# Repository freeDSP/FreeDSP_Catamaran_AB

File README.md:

# FreeDSP_Catamaran_AB
A dual mono construction Concept Differential ADC 1 in 4 out ADAU1701 board. Extreme High performance (ADC to DAC Overall Distortion 0.00087%) differential A/D Conversion, differential RCA-pin Outputs, fs=96kHz, 8 slots TDM-Interlink across the boards.

Features:

- 1in 4 out RCA jacks on each PCB (2 boards requires for stereo use)
- High-performance differential monaural ADAU1701 ADC circuit
- GND lift-able Differntial RCA-pin Input curcuit
- GND lift-able Differential RCA-pin Output circuit
- Mains Power Switch
- Power-ON/OFF/Reboot Anti-Pop Audio Mute
- LED Power Indicator
- MP1/MP7 controlled LED Indicators
- A/B Program Select switch with Auto-Reboot feature
- Selectable DSP reboot Dual-EEPROMs
- Rotary Pots for AUXADC 0-3
- interlink header for AUXADC control voltage 0-3 and Reset
- Common-mode Choke filtered Power Supply Input
- 0805(2.0mm x 1.25mm) SMD Resistors & Capacitors
- Prepare for the through-hole Ele-Caps on the Audio Path
- Unity Gain Analog Audio Input and Output (2V RMS)
- Absolute Phase transparent. (No need to invert Output Phase)
- Buffered TDM Interlink I/O Header (with Enable control)
- JST-EH Connectors for Optional XLR output driver board.

PCBA file package included in JLPCB_OrderFiles. You can order SMT and Boards. (https://jlcpcb.com/) 

A Wiki Page(https://github.com/freeDSP/FreeDSP_Catamaran_AB/wiki) of this project

Discussion forum thread (https://www.diyaudio.com/community/threads/freedsp-catamaran-a-b.381417/)

Project web page: (Direct Link) https://cyberpithilo.web.fc2.com/audio/freedsp/index.html

Project web page: (Yandex Machine Translation) https://translate.yandex.com/translate?url=https%3A%2F%2Fcyberpithilo.web.fc2.com%2Faudio%2Ffreedsp%2Fcatamaran_main.html&lang=ja-en

Project web page: (Google Machine Translation) https://cyberpithilo-web-fc2-com.translate.goog/audio/freedsp/catamaran_main.html?_x_tr_sl=ja&_x_tr_tl=en&_x_tr_hl=ja

# License
This work and all other materials under https://github.com/freeDSP are licensed under a Creative Commons Attribution Share-Alike 4.0 license. This allows for both personal and commercial derivative works, as long as they credit freeDSP and release their designs under the same license.

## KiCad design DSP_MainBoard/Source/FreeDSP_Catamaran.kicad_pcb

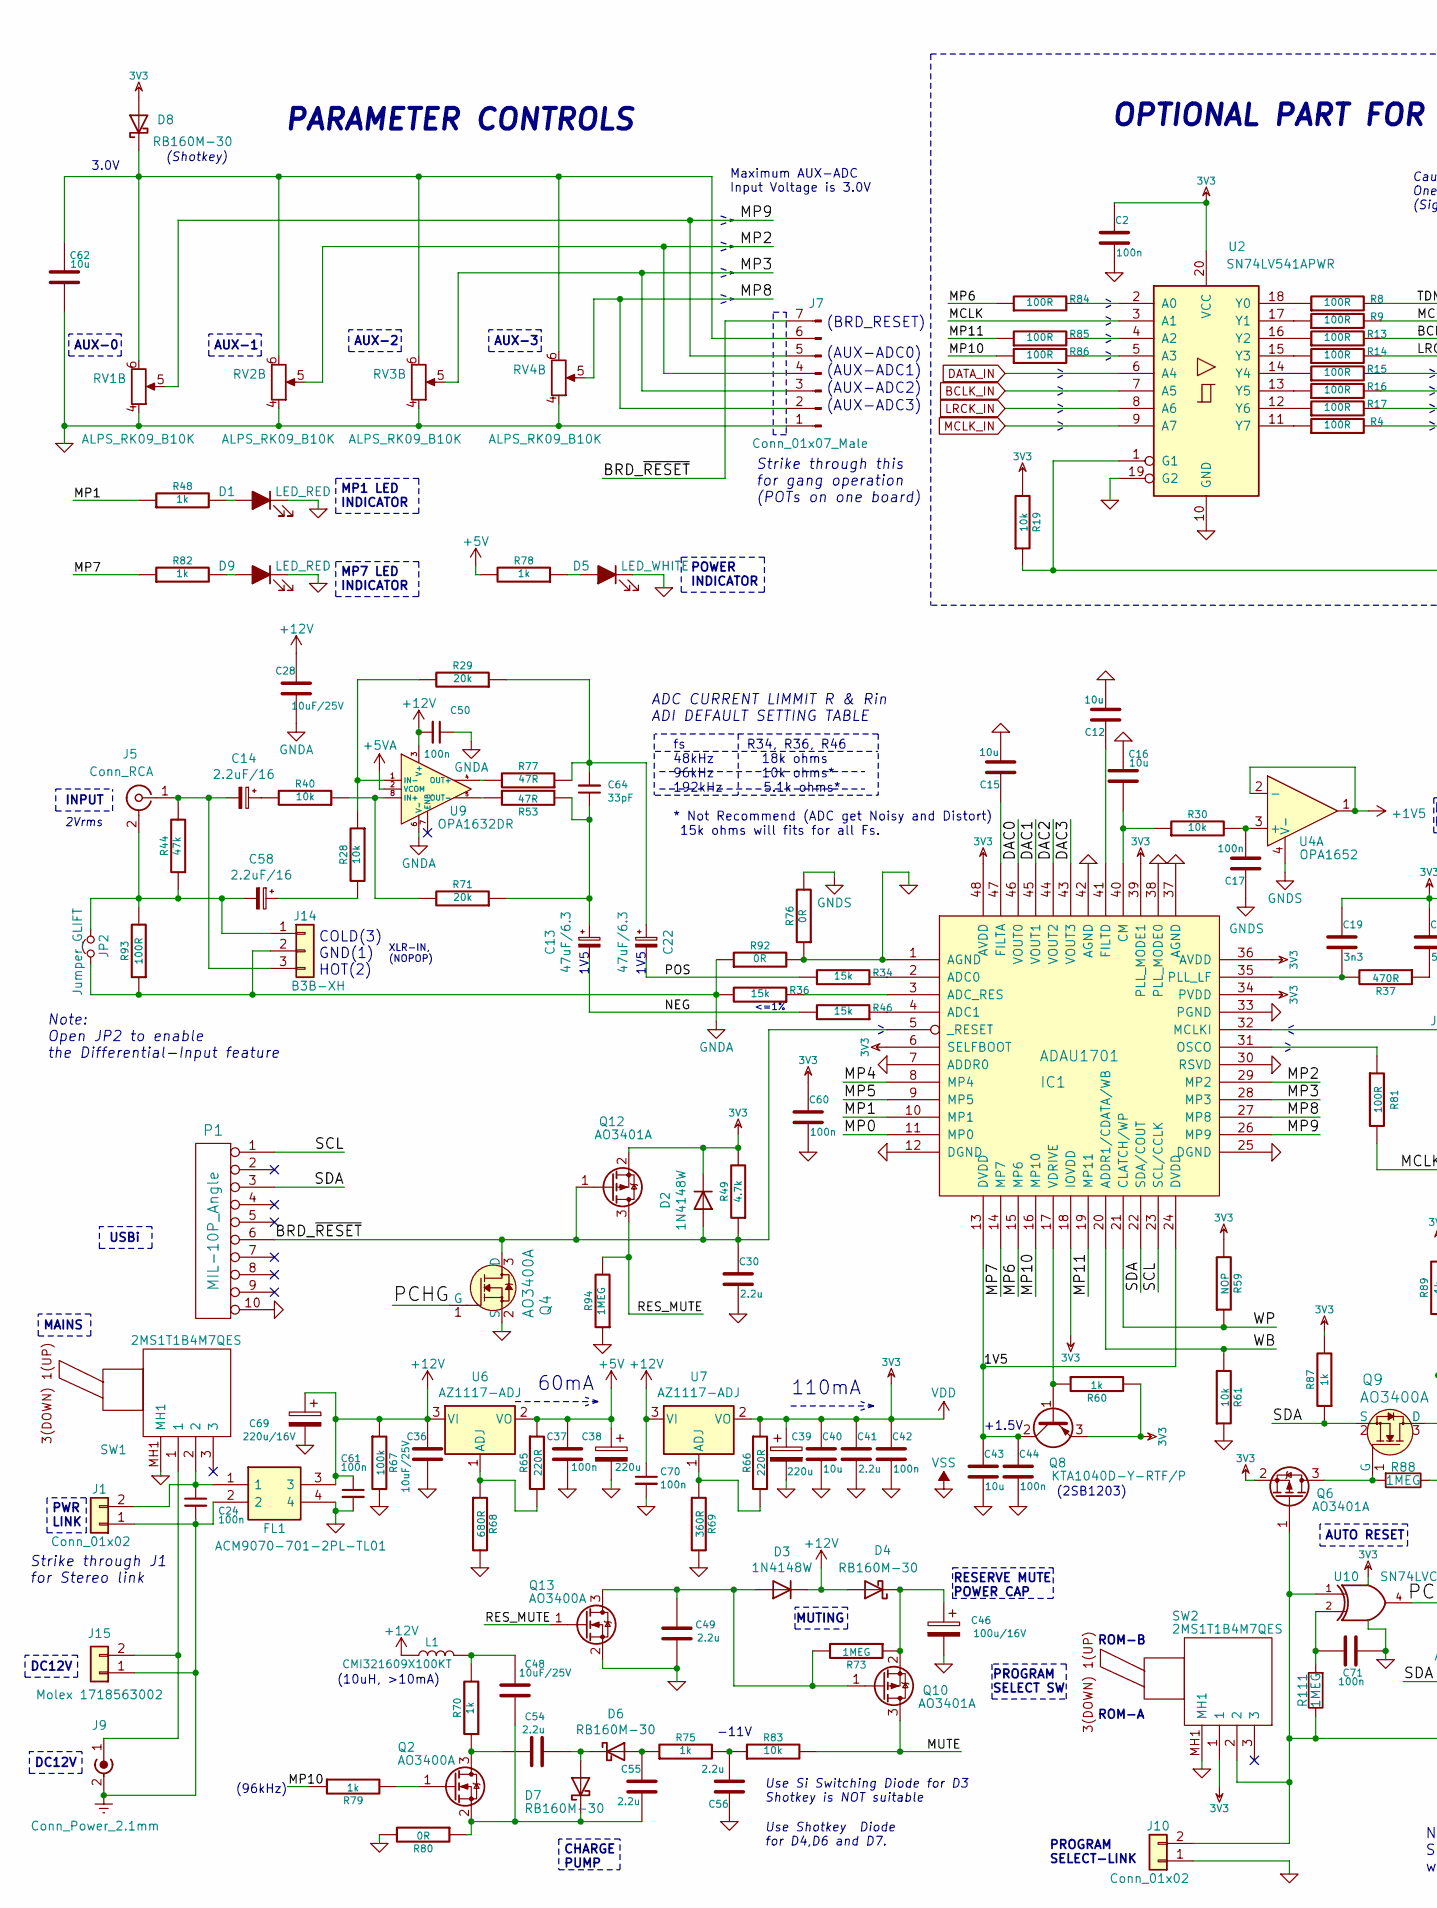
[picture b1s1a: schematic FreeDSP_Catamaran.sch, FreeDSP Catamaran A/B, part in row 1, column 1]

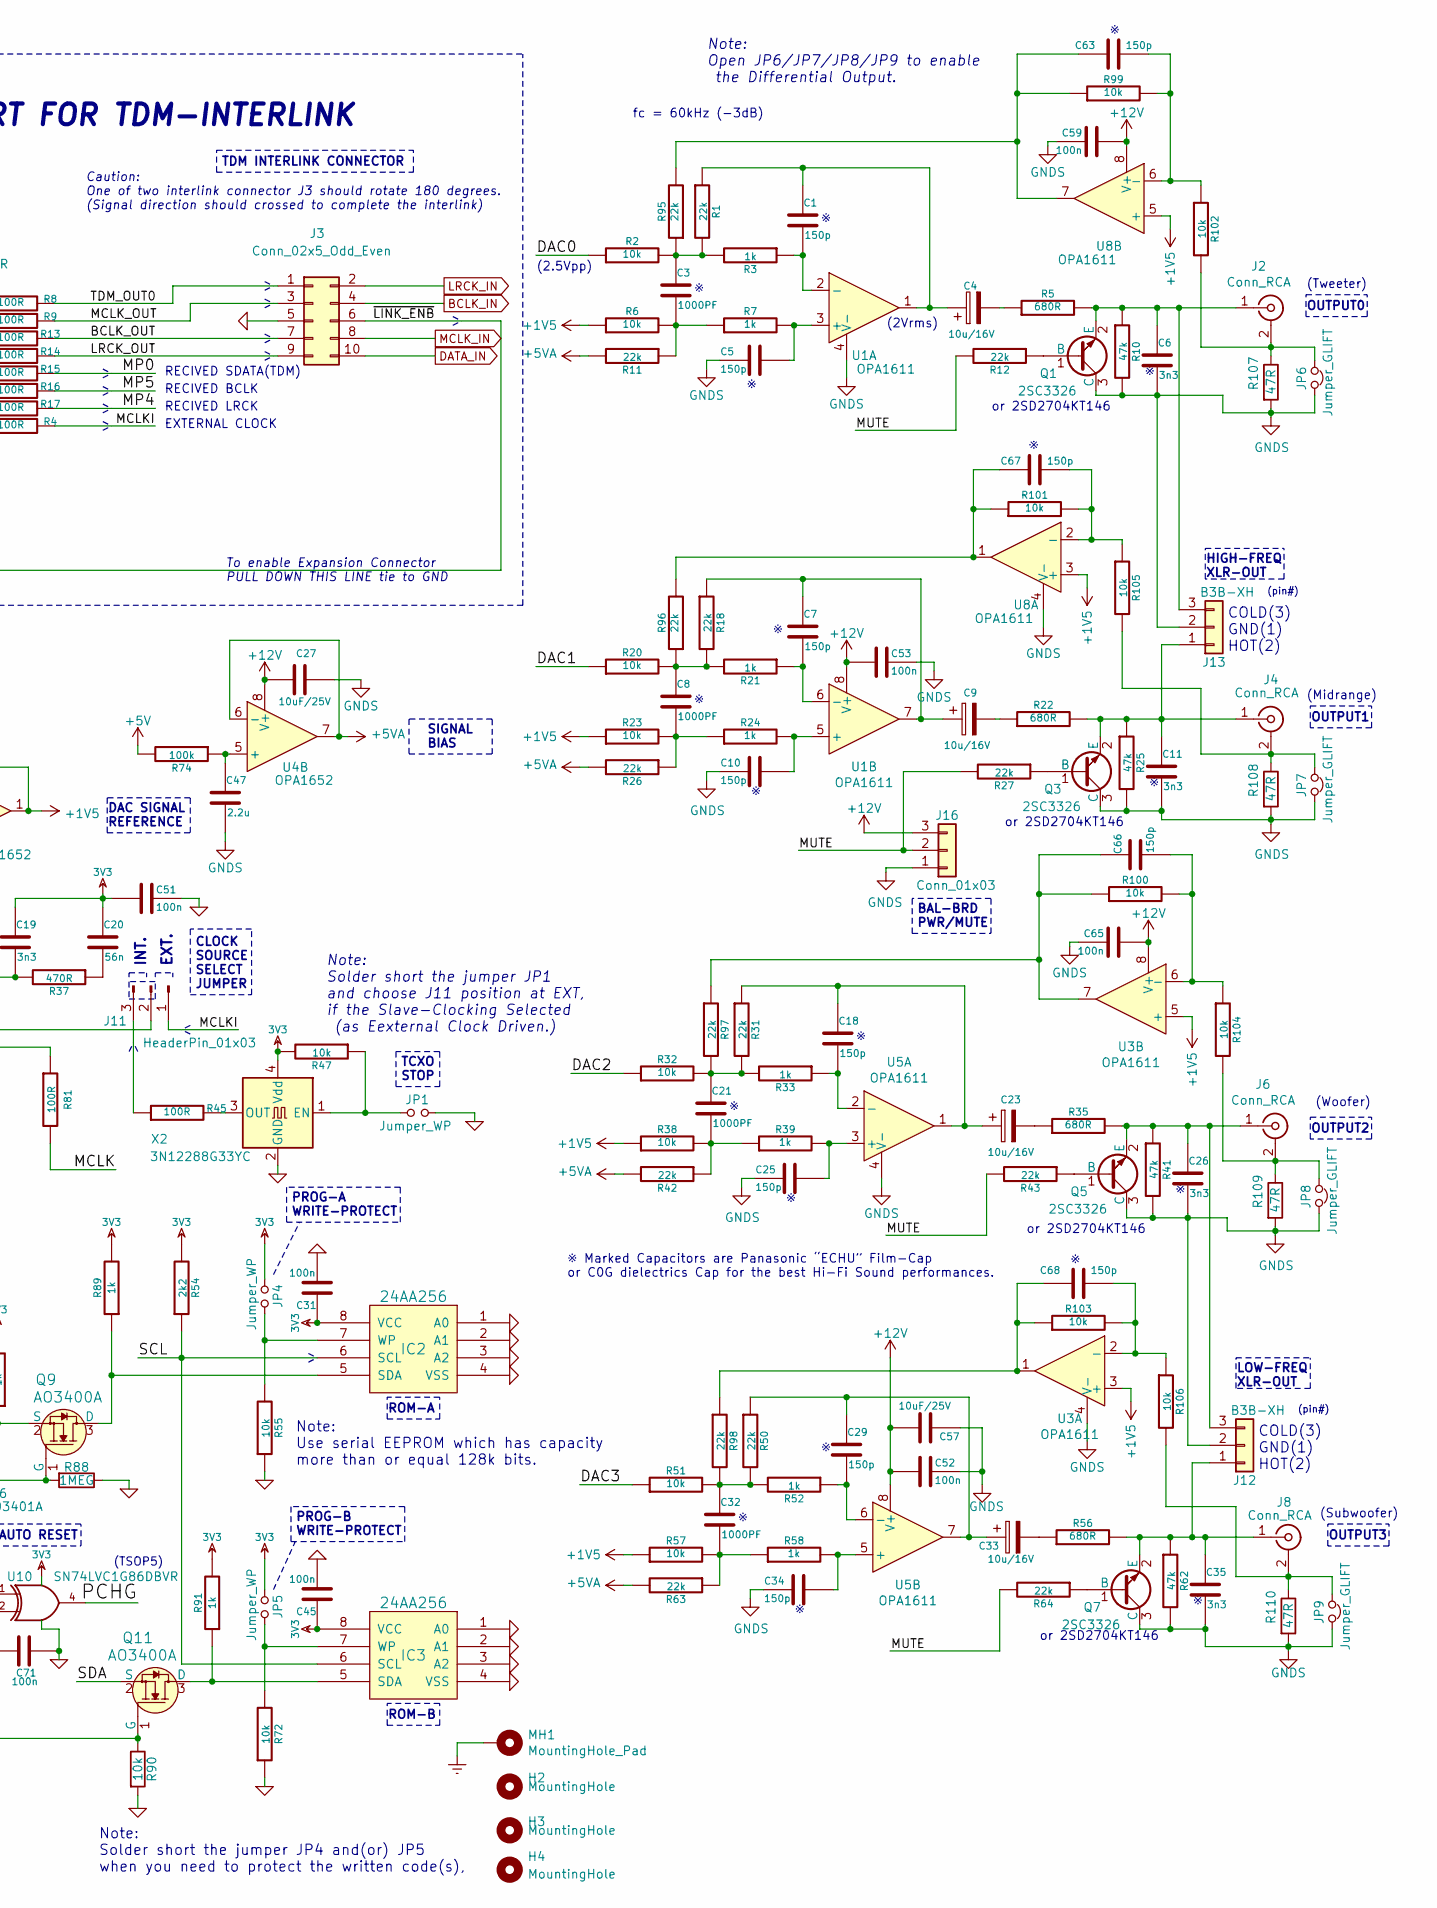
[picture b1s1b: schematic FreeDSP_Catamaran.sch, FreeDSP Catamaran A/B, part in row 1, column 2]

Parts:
C1, C5, C7, C10, C18, C25, C29, C34, C63, C66, C67, C68: 150p; C_0805_HandSoldering
C2, C17, C24, C31, C37, C42, C44, C45, C50, C51, C52, C53, C59, C60, C61, C65, C70, C71: 100n; C_0805_HandSoldering
C3, C8, C21, C32: 1000PF; C_0805_HandSoldering
C4, C9, C23, C33: 10u/16V; CP_Radial_D5.0mm_P2.00mm
C6, C11, C19, C26, C35: 3n3; C_0805_HandSoldering
C12, C15, C16, C40, C43, C62: 10u; C_0805_HandSoldering
C13, C22: 47uF/6.3; CP_Combo_D5.0mm_P2-5mm
C14, C58: 2.2uF/16; CP_Combo_D5.0mm_P2-5mm
C20: 56n; C_0805_HandSoldering
C27, C28, C36, C48, C57: 10uF/25V; C_0805_HandSoldering
C30, C41, C47, C49, C54, C55, C56: 2.2u; C_0805_HandSoldering
C38, C39: 220u; CP_Radial_D8.0mm_P5.00mm
C46: 100u/16V; CP_Radial_D6.3mm_P2.50mm
C64: 33pF; C_0805_HandSoldering
C69: 220u/16V; CP_Radial_D8.0mm_P5.00mm
D1, D9: LED_RED; LED_0603_HandSoldering
D2, D3: 1N4148W; D_SOD-123
D4, D6, D7, D8: RB160M-30; D_SOD-123
D5: LED_WHITE; LED_0603_HandSoldering
FL1: ACM9070-701-2PL-TL01; Manufacturer_Part_Number ACM9070-701-2PL-TL01
H2, H3, H4: MountingHole; MountingHole_3.2mm_M3_Pad
IC1: ADAU1701; LQFP-48_7x7mm_Pitch0.5mm
IC2, IC3: 24AA256; SOIC-8_3.9x4.9mm_Pitch1.27mm
J1, J10: Conn_01x02; PinHeader_1x02_P2.54mm_Vertical
J2, J4, J5, J6, J8: Conn_RCA; RJ-2410N
J3: Conn_02x5_Odd_Even; IDC-Header_2x05_P2.54mm_Vertical
J7: Conn_01x07_Male; PinHeader_1x07_P2.54mm_Vertical
J9: Conn_Power_2.1mm; BARREL_JACK
J11: HeaderPin_01x03; PinHeader_1x03_P2.54mm_Vertical
J12, J13, J14: B3B-XH; JST_XH_B3B-XH-AM_1x03_P2.50mm_Vertical
J15: Molex 1718563002; Molex_KK-254_AE-6410-02A_1x02_P2.54mm_Vertical
J16: Conn_01x03; PinHeader_1x03_P2.54mm_Vertical
JP1, JP4, JP5: Jumper_WP; SolderJumper-2_P1.3mm_Open_RoundedPad1.0x1.5mm
JP2, JP6, JP7, JP8, JP9: Jumper_GLIFT; SolderJumper-2_P1.3mm_Open_RoundedPad1.0x1.5mm
L1: CMI321609X100KT; Inductor_1212; MPN LQH2MCN100K02L
MH1: MountingHole_Pad; MountingHole_3.2mm_M3_Pad_Via
P1: MIL-10P_Angle; IDC-Header_2x05_P2.54mm_Vertical
Q1, Q3, Q5, Q7: 2SC3326; SOT-23
Q2, Q13: AO3400A; SOT-23
Q4, Q9, Q11: AO3400A; SOT-23-3; MPN 2N7002; Digi-Key_PN 2N7002NCT-ND
Q6, Q10, Q12: AO3401A; SOT-23
Q8: KTA1040D-Y-RTF/P; TO-252-2
R1, R11, R12, R18, R26, R27, R31, R42, R43, R50, R63, R64, R95, R96, R97, R98: 22k; R_0805_HandSoldering
R2, R6, R19, R20, R23, R28, R30, R32, R38, R40, R47, R51, R55, R57, R61, R72, R83, R90, R99, R100, R101, R102, R103, R104, R105, R106: 10k; R_0805_HandSoldering
R3, R7, R21, R24, R33, R39, R48, R52, R58, R60, R70, R75, R78, R79, R82, R87, R89, R91: 1k; R_0805_HandSoldering
R4, R8, R9, R13, R14, R15, R16, R17, R45, R81, R84, R85, R86, R93: 100R; R_0805_HandSoldering
R5, R22, R35, R56, R68: 680R; R_0805_HandSoldering
R10, R25, R41, R44, R62: 47k; R_0805_HandSoldering
R29, R71: 20k; R_0805_HandSoldering
R34, R36, R46: 15k; R_0805_HandSoldering
R37: 470R; R_0805_HandSoldering
R49: 4.7k; R_0805_HandSoldering
R53, R77, R107, R108, R109, R110: 47R; R_0805_HandSoldering
R54: 2k2; R_0805_HandSoldering
R59: NOP; R_0805_HandSoldering
R65, R66: 220R; R_0805_HandSoldering
R67, R74: 100k; R_0805_HandSoldering
R69: 360R; R_0805_HandSoldering
R73, R88, R94, R111: 1MEG; R_0805_HandSoldering
R76, R80, R92: 0R; R_0805_HandSoldering
RV1, RV2, RV3, RV4: ALPS_RK09_B10K; Potentiometer_Alps_RK09L_Double_Vertical
SW1, SW2: 2MS1T1B4M7QES; Manufacturer_Part_Number 2MS1T1B4M7QES
U1, U3, U5, U8: OPA1611; SOIC127P600X175-8N
U2: SN74LV541APWR; TSSOP-20_W4.4mm
U4: OPA1652; SOIC127P600X175-8N
U6, U7: AZ1117-ADJ; SOT-223-3_TabPin2
U9: OPA1632DR; SOIC127P600X175-8N
U10: SN74LVC1G86DBVR; TSOT-23-5
X2: 3N12288G33YC; Oscillator_SMD_Abracon_ASE-4Pin_3.2x2.5mm

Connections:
3V3: C2.1, C19.1, C20.1, C31.1, C39.1, C40.1, C41.1, C42.1, C45.1, C51.2, C60.1, D2.1 (K), D8.2 (A), IC1.6 (SELFBOOT), IC1.18 (IOVDD), IC1.34 (PVDD), IC1.36 (AVDD), IC1.39 (PLL_MODE1), IC1.48 (AVDD), IC2.8 (VCC), IC3.8 (VCC), JP4.2, JP5.2, Q6.2 (S), Q8.3 (E), Q12.2 (S), R19.2, R47.2, R49.2, R54.2, R59.2, R60.2, R66.1, R87.2, R89.2, R91.2, SW2.1, U2.20 (VCC), U7.2 (VO), U10.5 (VCC), X2.4 (Vdd)
+1V5: R6.1, R23.1, R38.1, R57.1, U3.3 (+), U3.5 (+), U4.1, U4.2 (-), U8.3 (+), U8.5 (+)
+5V: C37.1, C38.1, R65.1, R74.2, R78.2, U6.2 (VO)
+5VA: R11.2, R26.2, R42.2, R63.2, U4.6 (-), U4.7, U9.2 (VCOM)
+12V: C27.2, C28.1, C36.1, C50.2, C52.2, C53.2, C57.1, C59.2, C61.1, C65.2, C69.1, C70.1, D3.1 (K), D4.2 (A), FL1.3, J16.3, L1.1, R67.1, U1.8 (V+), U3.8 (V+), U4.8 (V+), U5.8 (V+), U6.3 (VI), U7.3 (VI), U8.8 (V+), U9.3 (V+)
/1V5: C43.1, C44.1, IC1.13 (DVDD), IC1.24 (DVDD), Q8.2 (C)
/BCLK_OUT: J3.7, R13.2
/BRD_~RESET: C30.1, D2.2 (A), IC1.5 (_RESET), J7.7, P1.6, Q4.3 (D), Q12.1 (G), R49.1
/DAC0: IC1.46 (VOUT0), R2.1
/DAC1: IC1.45 (VOUT1), R20.1
/DAC2: IC1.44 (VOUT2), R32.1
/DAC3: IC1.43 (VOUT3), R51.1
/LRCK_OUT: J3.9, R14.2
/MCLK: R81.2, U2.3 (A1)
/MCLKI: J11.1, R4.2
/MCLK_OUT: J3.3, R9.2
/MP0: IC1.11 (MP0), R15.2
/MP1: IC1.10 (MP1), R48.1
/MP2: IC1.29 (MP2), J7.4, RV2.5
/MP3: IC1.28 (MP3), J7.3, RV3.5
/MP4: IC1.8 (MP4), R17.2
/MP5: IC1.9 (MP5), R16.2
/MP6: IC1.15 (MP6), R84.1
/MP7: IC1.14 (MP7), R82.1
/MP8: IC1.27 (MP8), J7.2, RV4.5
/MP9: IC1.26 (MP9), J7.5, RV1.5
/MP10: IC1.16 (MP10), R79.1, R86.1
/MP11: IC1.19 (MP11), R85.1
/MUTE: J16.2, Q10.3 (D), R12.2, R27.2, R43.2, R64.2, R83.2
/NEG: C13.2, R46.2
/PCHG: Q4.1 (G), U10.4
/POS: C22.2, R34.2
/RES_MUTE: Q12.3 (D), Q13.1 (G), R94.2
/SCL: IC1.23 (SCL/CCLK), IC2.6 (SCL), IC3.6 (SCL), P1.1, R54.1
/SDA: IC1.22 (SDA/COUT), P1.3, Q9.2 (S), Q11.2 (S), R87.1
/TDM_OUT0: J3.1, R8.2
/WB: IC1.20 (ADDR1/CDATA/WB), R61.2
/WP: IC1.21 (CLATCH/WP), R59.1
/~LINK_ENB: J3.6, R19.1, U2.1 (G1)
BCLK_IN: J3.4, U2.7 (A5)
DATA_IN: J3.10, U2.6 (A4)
Earth: C24.2, FL1.2, J1.1, J9.2 (Ext), J15.1, MH1.1
GND: C2.2, C12.2, C15.2, C16.2, C30.2, C31.2, C36.2, C37.2, C38.2, C39.2, C40.2, C41.2, C42.2, C43.2, C44.2, C45.2, C46.2, C49.2, C51.1, C56.1, C60.2, C61.2, C62.1, C69.2, C70.2, C71.1, D1.1 (K), D5.1 (K), D9.1 (K), FL1.4, IC1.1 (AGND), IC1.7 (ADDR0), IC1.12 (DGND), IC1.25 (DGND), IC1.30 (RSVD), IC1.33 (PGND), IC1.37 (AGND), IC1.38 (PLL_MODE0), IC1.42 (AGND), IC2.1 (A0), IC2.2 (A1), IC2.3 (A2), IC2.4 (VSS), IC3.1 (A0), IC3.2 (A1), IC3.3 (A2), IC3.4 (VSS), J3.5, J7.1, J10.1, JP1.1, P1.10, Q4.2 (S), Q13.2 (S), R55.1, R61.1, R67.2, R68.2, R69.2, R72.1, R76.1, R80.2, R88.1, R90.2, R92.2, R94.1, RV1.4, RV2.4, RV3.4, RV4.4, SW1.MH1, SW2.MH1, U2.10 (GND), U2.19 (G2), U10.3 (GND), X2.2 (GND)
GNDA: C28.2, C50.1, J14.2, JP2.1, R36.2, R92.1, R93.1, U9.6 (V-)
GNDS: C5.2, C6.2, C10.2, C11.2, C17.1, C25.2, C26.2, C27.1, C34.2, C35.2, C47.2, C52.1, C53.1, C57.2, C59.1, C65.1, J12.2, J13.2, J16.1, JP6.2, JP7.2, JP8.2, JP9.2, Q1.3 (C), Q3.3 (C), Q5.3 (C), Q7.3 (C), R10.2, R25.2, R41.2, R62.2, R76.2, R107.2, R108.2, R109.2, R110.2, U1.4 (V-), U3.4 (V-), U4.4 (V-), U5.4 (V-), U8.4 (V-)
LRCK_IN: J3.2, U2.8 (A6)
MCLK_IN: J3.8, U2.9 (A7)
unnamed: C1.1, C4.1, R1.1, U1.1
unnamed: C1.2, R3.1, U1.2 (-)
unnamed: C3.1, R1.2, R2.2, R3.2, R95.1
unnamed: C3.2, R6.2, R7.1, R11.1
unnamed: C4.2, R5.1
unnamed: C5.1, R7.2, U1.3 (+)
unnamed: C6.1, J2.1 (In), J13.3, Q1.2 (E), R5.2, R10.1
unnamed: C7.1, C9.1, R18.1, U1.7
unnamed: C7.2, R21.1, U1.6 (-)
unnamed: C8.1, R18.2, R20.2, R21.2, R96.1
unnamed: C8.2, R23.2, R24.1, R26.1
unnamed: C9.2, R22.1
unnamed: C10.1, R24.2, U1.5 (+)
unnamed: C11.1, J4.1 (In), J13.1, Q3.2 (E), R22.2, R25.1
unnamed: C12.1, IC1.41 (FILTD)
unnamed: C13.1, C64.1, R53.2, R71.1
unnamed: C14.1, R40.2
unnamed: C14.2, J5.1 (In), J14.3, R44.2
unnamed: C15.1, IC1.47 (FILTA)
unnamed: C16.1, IC1.40 (CM), R30.1
unnamed: C17.2, R30.2, U4.3 (+)
unnamed: C18.1, C23.1, R31.1, U5.1
unnamed: C18.2, R33.1, U5.2 (-)
unnamed: C19.2, IC1.35 (PLL_LF), R37.2
unnamed: C20.2, R37.1
unnamed: C21.1, R31.2, R32.2, R33.2, R97.2
unnamed: C21.2, R38.2, R39.1, R42.1
unnamed: C22.1, C64.2, R29.1, R77.1
unnamed: C23.2, R35.1
unnamed: C24.1, FL1.1, J1.2, SW1.2
unnamed: C25.1, R39.2, U5.3 (+)
unnamed: C26.1, J6.1 (In), J12.3, Q5.2 (E), R35.2, R41.1
unnamed: C29.1, C33.1, R50.1, U5.7
unnamed: C29.2, R52.1, U5.6 (-)
unnamed: C32.1, R50.2, R51.2, R52.2, R98.2
unnamed: C32.2, R57.2, R58.1, R63.1
unnamed: C33.2, R56.1
unnamed: C34.1, R58.2, U5.5 (+)
unnamed: C35.1, J8.1 (In), J12.1, Q7.2 (E), R56.2, R62.1
unnamed: C46.1, D4.1 (K), Q10.2 (S), R73.1
unnamed: C47.1, R74.1, U4.5 (+)
unnamed: C48.1, L1.2, R70.2
unnamed: C48.2, C55.2, D7.1 (K), Q2.2 (S), R80.1
unnamed: C49.1, D3.2 (A), Q10.1 (G), Q13.3 (D), R73.2
unnamed: C54.1, Q2.3 (D), R70.1
unnamed: C54.2, D6.1 (K), D7.2 (A)
unnamed: C55.1, D6.2 (A), R75.1
unnamed: C56.2, R75.2, R83.1
unnamed: C58.1, R28.2
unnamed: C58.2, J5.2 (Ext), J14.1, JP2.2, R44.1, R93.2
unnamed: C62.2, D8.1 (K), J7.6, RV1.6, RV2.6, RV3.6, RV4.6
unnamed: C63.1, R95.2, R99.1, U8.7
unnamed: C63.2, R99.2, R102.1, U8.6 (-)
unnamed: C66.1, R97.1, R100.1, U3.7
unnamed: C66.2, R100.2, R104.1, U3.6 (-)
unnamed: C67.1, R96.2, R101.1, U8.1
unnamed: C67.2, R101.2, R105.1, U8.2 (-)
unnamed: C68.1, R98.1, R103.1, U3.1
unnamed: C68.2, R103.2, R106.1, U3.2 (-)
unnamed: C71.2, R111.2, U10.2
unnamed: D1.2 (A), R48.2
unnamed: D5.2 (A), R78.1
unnamed: D9.2 (A), R82.2
unnamed: IC1.2 (ADC0), R34.1
unnamed: IC1.3 (ADC_RES), R36.1
unnamed: IC1.4 (ADC1), R46.1
unnamed: IC1.17 (VDRIVE), Q8.1 (B), R60.1
unnamed: IC1.31 (OSCO), R81.1
unnamed: IC1.32 (MCLKI), J11.2
unnamed: IC2.5 (SDA), Q9.3 (D), R89.1
unnamed: IC2.7 (WP), JP4.1, R55.2
unnamed: IC3.5 (SDA), Q11.3 (D), R91.1
unnamed: IC3.7 (WP), JP5.1, R72.2
unnamed: J2.2 (Ext), JP6.1, R102.2, R107.1
unnamed: J4.2 (Ext), JP7.1, R105.2, R108.1
unnamed: J6.2 (Ext), JP8.1, R104.2, R109.1
unnamed: J8.2 (Ext), JP9.1, R106.2, R110.1
unnamed: J10.2, Q6.1 (G), Q11.1 (G), R90.1, R111.1, SW2.2, U10.1
unnamed: J11.3, R45.1
unnamed: J9.1 (In), J15.2, SW1.1
unnamed: JP1.2, R47.1, X2.1 (EN)
unnamed: Q1.1 (B), R12.1
unnamed: Q2.1 (G), R79.2
unnamed: Q3.1 (B), R27.1
unnamed: Q5.1 (B), R43.1
unnamed: Q6.3 (D), Q9.1 (G), R88.2
unnamed: Q7.1 (B), R64.1
unnamed: R4.1, U2.11 (Y7)
unnamed: R8.1, U2.18 (Y0)
unnamed: R9.1, U2.17 (Y1)
unnamed: R13.1, U2.16 (Y2)
unnamed: R14.1, U2.15 (Y3)
unnamed: R15.1, U2.14 (Y4)
unnamed: R16.1, U2.13 (Y5)
unnamed: R17.1, U2.12 (Y6)
unnamed: R28.1, R29.2, U9.1 (IN-)
unnamed: R40.1, R71.2, U9.8 (IN+)
unnamed: R45.2, X2.3 (OUT)
unnamed: R53.1, U9.5 (OUT-)
unnamed: R65.2, R68.1, U6.1 (ADJ)
unnamed: R66.2, R69.1, U7.1 (ADJ)
unnamed: R77.2, U9.4 (OUT+)
unnamed: R84.2, U2.2 (A0)
unnamed: R85.2, U2.4 (A2)
unnamed: R86.2, U2.5 (A3)

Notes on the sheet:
<=1%
AUTO RESET
RECIVED LRCK
RECIVED BCLK
RECIVED SDATA(TDM)
TDM INTERLINK CONNECTOR
AUX-0
AUX-1
USBi
DC12V
fc = 60kHz (-3dB)
(2.5Vpp)
(2Vrms)
MUTING
INPUT
OUTPUT0
OUTPUT1
OUTPUT2
OUTPUT3
PROGRAM SELECT SW
DAC SIGNAL REFERENCE
SIGNAL BIAS
PROG-B WRITE-PROTECT
OPTIONAL PART FOR TDM-INTERLINK
Note: Use serial EEPROM which has capacity more than or equal 128k bits.
ROM-A
ROM-B
(AUX-ADC1)
(AUX-ADC0)
or 2SD2704KT146
RESERVE MUTE POWER CAP
Use Si Switching Diode for D3 Shotkey is NOT suitable
※ Marked Capacitors are Panasonic “ECHU” Film-Cap or C0G dielectrics Cap for the best Hi-Fi Sound performances.
POWER INDICATOR
CHARGE PUMP
(96kHz)
-11V
+1.5V
3.0V
Maximum AUX-ADC Input Voltage is 3.0V

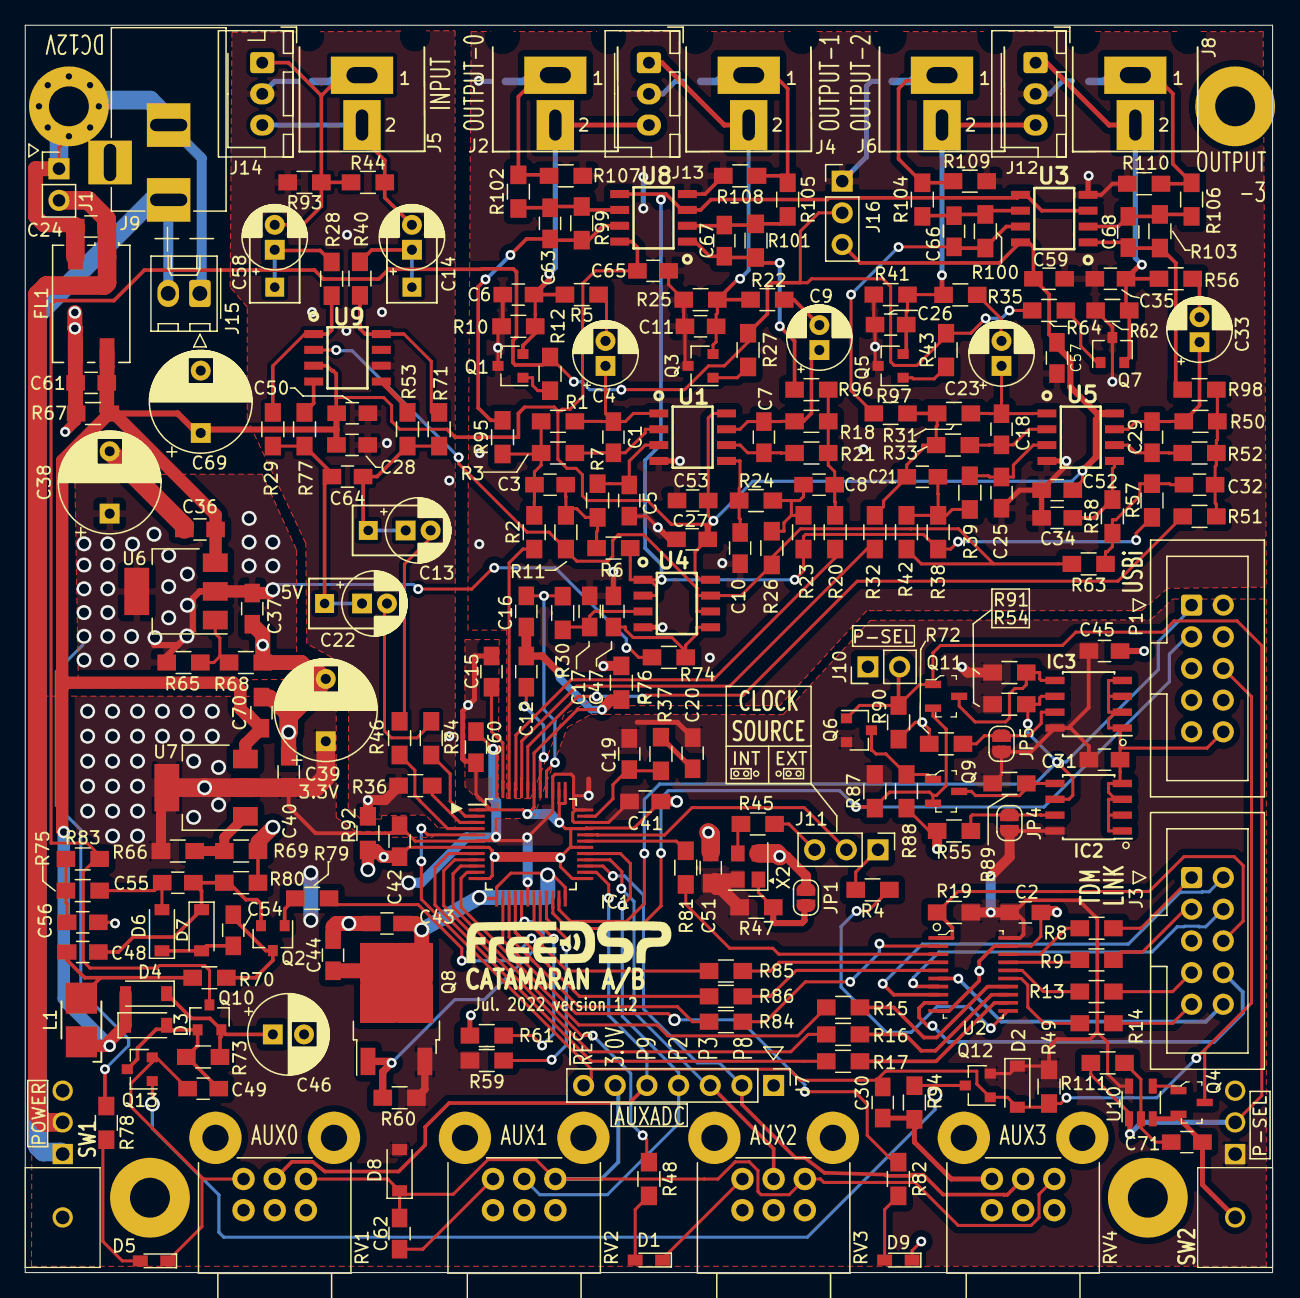
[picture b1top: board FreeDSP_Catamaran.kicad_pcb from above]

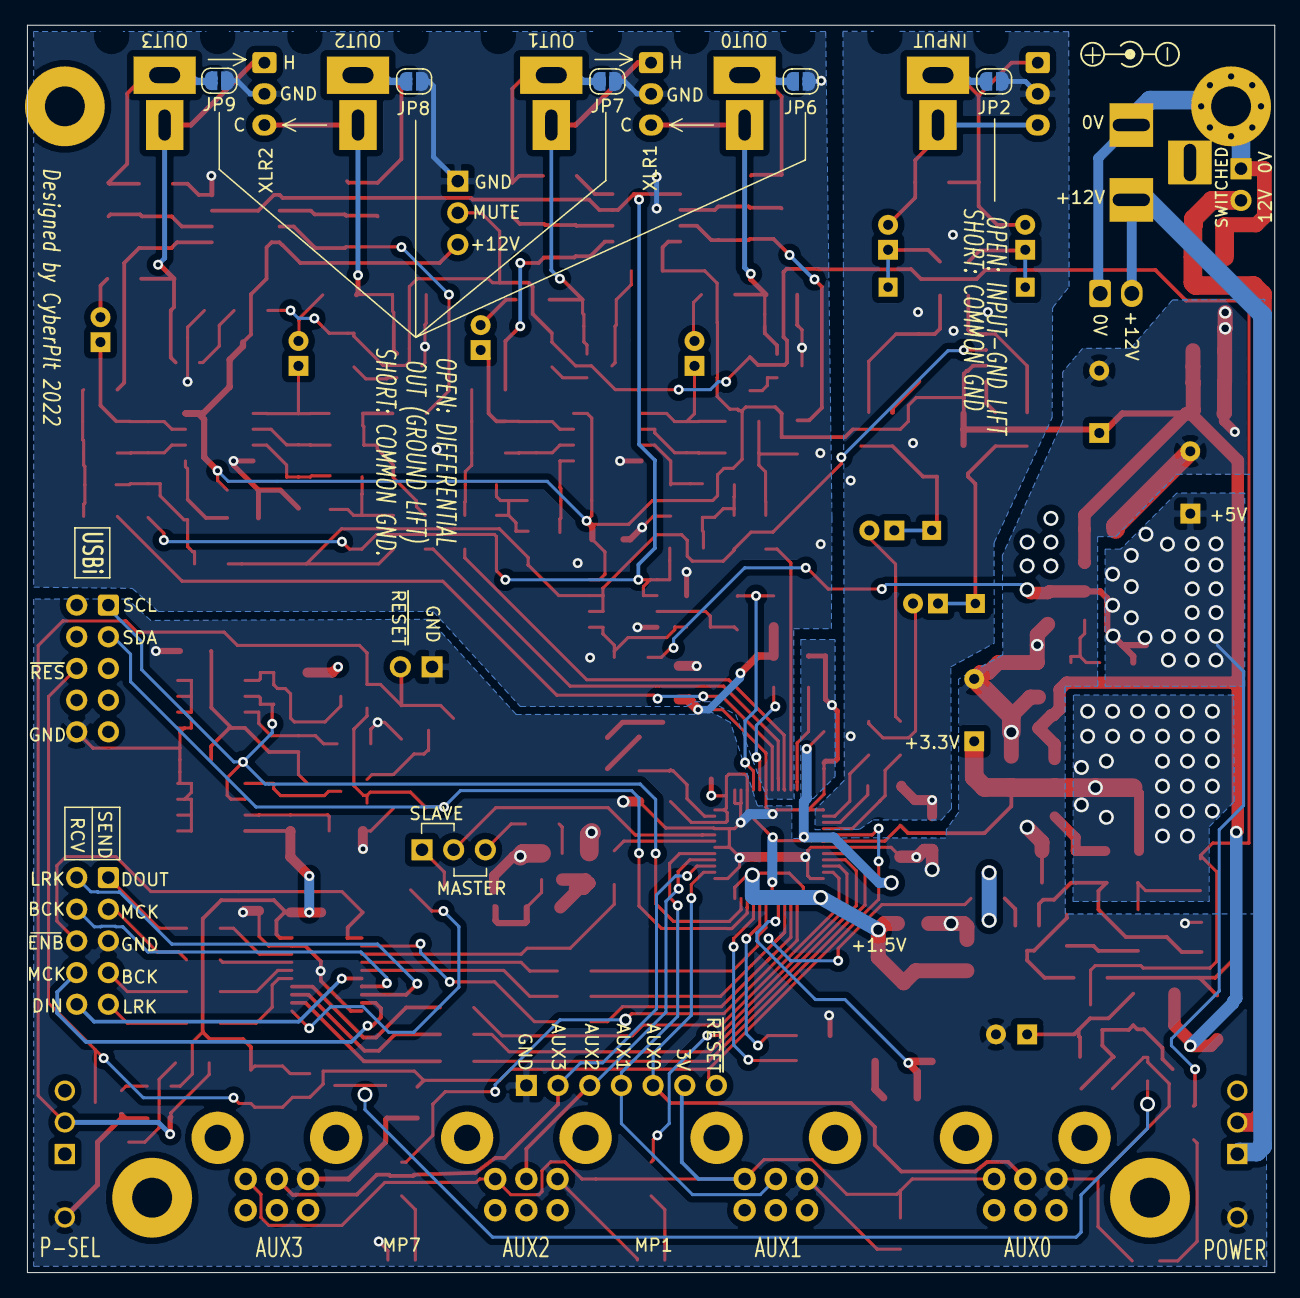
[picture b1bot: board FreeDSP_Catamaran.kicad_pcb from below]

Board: 2 copper layers, 100.0 x 100.0 mm, 255 parts (5 on the bottom side), 152 nets.

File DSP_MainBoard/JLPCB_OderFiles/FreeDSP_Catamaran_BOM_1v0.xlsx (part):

Comment | Designator | Footprint | JLCPCB Part #（optional）
150p | C1 | Capacitors_SMD:C_0805_HandSoldering | C159769
150p | C10 | Capacitors_SMD:C_0805_HandSoldering | C159769
3n3 | C11 | Capacitors_SMD:C_0805_HandSoldering | C129655
10u | C12 | Capacitors_SMD:C_0805_HandSoldering | C15850
10u | C15 | Capacitors_SMD:C_0805_HandSoldering | C15850
10u | C16 | Capacitors_SMD:C_0805_HandSoldering | C15850
100n | C17 | Capacitors_SMD:C_0805_HandSoldering | C49678
150p | C18 | Capacitors_SMD:C_0805_HandSoldering | C159769
3n3 | C19 | Capacitors_SMD:C_0805_HandSoldering | C129655
100n | C2 | Capacitors_SMD:C_0805_HandSoldering | C49678
56n | C20 | Capacitors_SMD:C_0805_HandSoldering | C1753
1000PF | C21 | Capacitors_SMD:C_0805_HandSoldering | C343010
100n | C24 | Capacitors_SMD:C_0805_HandSoldering | C49678
150p | C25 | Capacitors_SMD:C_0805_HandSoldering | C159769
3n3 | C26 | Capacitors_SMD:C_0805_HandSoldering | C129655
10uF/25V | C27 | Capacitors_SMD:C_0805_HandSoldering | C15850
10uF/25V | C28 | Capacitors_SMD:C_0805_HandSoldering | C15850
150p | C29 | Capacitors_SMD:C_0805_HandSoldering | C159769
1000PF | C3 | Capacitors_SMD:C_0805_HandSoldering | C343010
2.2u | C30 | Capacitors_SMD:C_0805_HandSoldering | C49217
100n | C31 | Capacitors_SMD:C_0805_HandSoldering | C49678
1000PF | C32 | Capacitors_SMD:C_0805_HandSoldering | C343010
150p | C34 | Capacitors_SMD:C_0805_HandSoldering | C159769
3n3 | C35 | Capacitors_SMD:C_0805_HandSoldering | C129655
10uF/25V | C36 | Capacitors_SMD:C_0805_HandSoldering | C15850
100n | C37 | Capacitors_SMD:C_0805_HandSoldering | C49678
10u | C40 | Capacitors_SMD:C_0805_HandSoldering | C15850
2.2u | C41 | Capacitors_SMD:C_0805_HandSoldering | C49217
100n | C42 | Capacitors_SMD:C_0805_HandSoldering | C49678
10u | C43 | Capacitors_SMD:C_0805_HandSoldering | C15850
100n | C44 | Capacitors_SMD:C_0805_HandSoldering | C49678
100n | C45 | Capacitors_SMD:C_0805_HandSoldering | C49678
2.2u | C47 | Capacitors_SMD:C_0805_HandSoldering | C49217
10uF/25V | C48 | Capacitors_SMD:C_0805_HandSoldering | C15850
2.2u | C49 | Capacitors_SMD:C_0805_HandSoldering | C49217
150p | C5 | Capacitors_SMD:C_0805_HandSoldering | C159769
100n | C50 | Capacitors_SMD:C_0805_HandSoldering | C49678
100n | C51 | Capacitors_SMD:C_0805_HandSoldering | C49678
100n | C52 | Capacitors_SMD:C_0805_HandSoldering | C49678
100n | C53 | Capacitors_SMD:C_0805_HandSoldering | C49678
2.2u | C54 | Capacitors_SMD:C_0805_HandSoldering | C49217
2.2u | C55 | Capacitors_SMD:C_0805_HandSoldering | C49217
2.2u | C56 | Capacitors_SMD:C_0805_HandSoldering | C49217
10uF/25V | C57 | Capacitors_SMD:C_0805_HandSoldering | C15850
100n | C59 | Capacitors_SMD:C_0805_HandSoldering | C49678
3n3 | C6 | Capacitors_SMD:C_0805_HandSoldering | C129655
100n | C60 | Capacitors_SMD:C_0805_HandSoldering | C49678
100n | C61 | Capacitors_SMD:C_0805_HandSoldering | C49678
10u | C62 | Capacitors_SMD:C_0805_HandSoldering | C15850
150p | C63 | Capacitors_SMD:C_0805_HandSoldering | C159769
33pF | C64 | Capacitors_SMD:C_0805_HandSoldering | C1814
100n | C65 | Capacitors_SMD:C_0805_HandSoldering | C49678
150p | C66 | Capacitors_SMD:C_0805_HandSoldering | C159769
150p | C67 | Capacitors_SMD:C_0805_HandSoldering | C159769
150p | C68 | Capacitors_SMD:C_0805_HandSoldering | C159769
150p | C7 | Capacitors_SMD:C_0805_HandSoldering | C159769
100n | C70 | Capacitors_SMD:C_0805_HandSoldering | C49678
1000PF | C8 | Capacitors_SMD:C_0805_HandSoldering | C343010
LED_RED | D1 | LEDs:LED_0603_HandSoldering | C2286
1N4148W | D2 | Diodes_SMD:D_SOD-123 | C81598
1N4148W | D3 | Diodes_SMD:D_SOD-123 | C81598
RB160M-30 | D4 | Diodes_SMD:D_SOD-123 | C8598
LED_WHITE | D5 | LEDs:LED_0603_HandSoldering | C2293
RB160M-30 | D6 | Diodes_SMD:D_SOD-123 | C8598
RB160M-30 | D7 | Diodes_SMD:D_SOD-123 | C8598
RB160M-30 | D8 | Diodes_SMD:D_SOD-123 | C8598
LED_RED | D9 | LEDs:LED_0603_HandSoldering | C2286
ACM9070-701-2PL-TL01 | FL1 | MyLibrary:ACM9070-701-2PL-TL01 | C14594
ADAU1701 | IC1 | Housings_QFP:LQFP-48_7x7mm_Pitch0.5mm | C26394
24AA256(or CAT24M01WI-GT3) | IC2 | Housings_SOIC:SOIC-8_3.9x4.9mm_Pitch1.27mm | C152172
24AA256(or CAT24M01WI-GT3) | IC3 | Housings_SOIC:SOIC-8_3.9x4.9mm_Pitch1.27mm | C152172
CMI321609X100KT | L1 | Inductors:Inductor_1212 | C1051
2SC3326 | Q1 | TO_SOT_Packages_SMD:SOT-23 | C27829
AO3401A | Q10 | TO_SOT_Packages_SMD:SOT-23 | C15127
AO3400A | Q11 | digikey-footprints:SOT-23-3 | C20917
AO3401A | Q12 | TO_SOT_Packages_SMD:SOT-23 | C15127
AO3400A | Q13 | TO_SOT_Packages_SMD:SOT-23 | C20917
AO3400A | Q2 | TO_SOT_Packages_SMD:SOT-23 | C20917
2SC3326 | Q3 | TO_SOT_Packages_SMD:SOT-23 | C27829
2SC3326 | Q5 | TO_SOT_Packages_SMD:SOT-23 | C27829
AO3401A | Q6 | TO_SOT_Packages_SMD:SOT-23 | C15127
2SC3326 | Q7 | TO_SOT_Packages_SMD:SOT-23 | C27829
KTA1040D-Y-RTF/P | Q8 | TO_SOT_Packages_SMD:TO-252-2 | C69791
AO3400A | Q9 | digikey-footprints:SOT-23-3 | C20917
22k | R1 | Resistors_SMD:R_0805_HandSoldering | C17560
47k | R10 | Resistors_SMD:R_0805_HandSoldering | C17713
10k | R100 | Resistors_SMD:R_0805_HandSoldering | C17414
10k | R101 | Resistors_SMD:R_0805_HandSoldering | C17414
10k | R102 | Resistors_SMD:R_0805_HandSoldering | C17414
10k | R103 | Resistors_SMD:R_0805_HandSoldering | C17414
10k | R104 | Resistors_SMD:R_0805_HandSoldering | C17414
10k | R105 | Resistors_SMD:R_0805_HandSoldering | C17414
10k | R106 | Resistors_SMD:R_0805_HandSoldering | C17414
47R | R107 | Resistors_SMD:R_0805_HandSoldering | C17714
47R | R108 | Resistors_SMD:R_0805_HandSoldering | C17714
47R | R109 | Resistors_SMD:R_0805_HandSoldering | C17714
22k | R11 | Resistors_SMD:R_0805_HandSoldering | C17560
47R | R110 | Resistors_SMD:R_0805_HandSoldering | C17714
22k | R12 | Resistors_SMD:R_0805_HandSoldering | C17560
100R | R13 | Resistors_SMD:R_0805_HandSoldering | C17408
100R | R14 | Resistors_SMD:R_0805_HandSoldering | C17408
100R | R15 | Resistors_SMD:R_0805_HandSoldering | C17408
100R | R16 | Resistors_SMD:R_0805_HandSoldering | C17408
100R | R17 | Resistors_SMD:R_0805_HandSoldering | C17408
22k | R18 | Resistors_SMD:R_0805_HandSoldering | C17560
10k | R19 | Resistors_SMD:R_0805_HandSoldering | C17414
10k | R2 | Resistors_SMD:R_0805_HandSoldering | C17414
10k | R20 | Resistors_SMD:R_0805_HandSoldering | C17414
1k | R21 | Resistors_SMD:R_0805_HandSoldering | C17513
680R | R22 | Resistors_SMD:R_0805_HandSoldering | C17798
10k | R23 | Resistors_SMD:R_0805_HandSoldering | C17414
1k | R24 | Resistors_SMD:R_0805_HandSoldering | C17513
47k | R25 | Resistors_SMD:R_0805_HandSoldering | C17713
22k | R26 | Resistors_SMD:R_0805_HandSoldering | C17560
22k | R27 | Resistors_SMD:R_0805_HandSoldering | C17560
10k | R28 | Resistors_SMD:R_0805_HandSoldering | C17414
10k | R29 | Resistors_SMD:R_0805_HandSoldering | C17414
1k | R3 | Resistors_SMD:R_0805_HandSoldering | C17513
10k | R30 | Resistors_SMD:R_0805_HandSoldering | C17414
22k | R31 | Resistors_SMD:R_0805_HandSoldering | C17560
10k | R32 | Resistors_SMD:R_0805_HandSoldering | C17414
1k | R33 | Resistors_SMD:R_0805_HandSoldering | C17513
18k | R34 | Resistors_SMD:R_0805_HandSoldering | C17506
680R | R35 | Resistors_SMD:R_0805_HandSoldering | C17798
18k | R36 | Resistors_SMD:R_0805_HandSoldering | C17506
470R | R37 | Resistors_SMD:R_0805_HandSoldering | C17710
10k | R38 | Resistors_SMD:R_0805_HandSoldering | C17414
1k | R39 | Resistors_SMD:R_0805_HandSoldering | C17513
100R | R4 | Resistors_SMD:R_0805_HandSoldering | C17408
10k | R40 | Resistors_SMD:R_0805_HandSoldering | C17414
47k | R41 | Resistors_SMD:R_0805_HandSoldering | C17713
22k | R42 | Resistors_SMD:R_0805_HandSoldering | C17560
22k | R43 | Resistors_SMD:R_0805_HandSoldering | C17560
47k | R44 | Resistors_SMD:R_0805_HandSoldering | C17713
100R | R45 | Resistors_SMD:R_0805_HandSoldering | C17408
18k | R46 | Resistors_SMD:R_0805_HandSoldering | C17506
10k | R47 | Resistors_SMD:R_0805_HandSoldering | C17414
1k | R48 | Resistors_SMD:R_0805_HandSoldering | C17513
4.7k | R49 | Resistors_SMD:R_0805_HandSoldering | C17673
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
